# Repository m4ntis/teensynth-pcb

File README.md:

# teensynth-pcb
KiCad PCB schematics for teensynth

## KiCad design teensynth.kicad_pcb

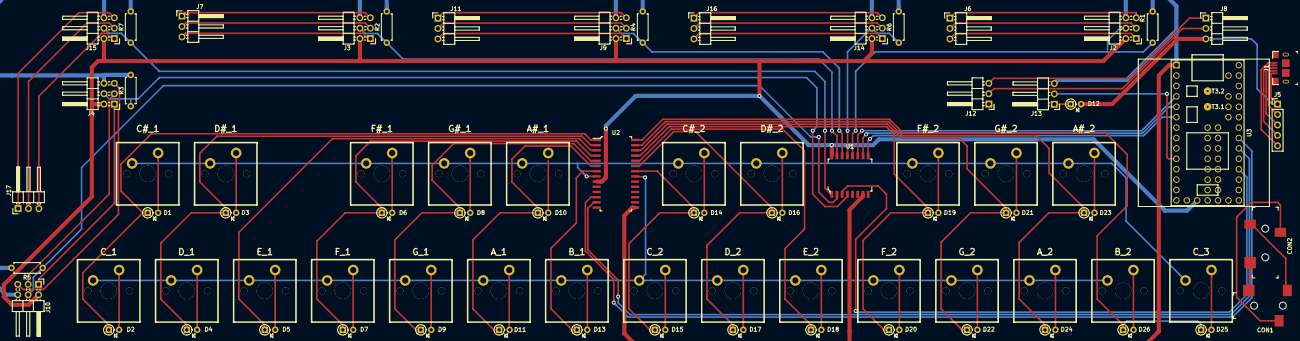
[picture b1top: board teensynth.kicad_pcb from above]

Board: 2 copper layers, 80 parts (0 on the bottom side), 86 nets.

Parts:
CON1, CON2: SJ-3523-SMT-TR; Switch_Slide_11.6x4mm_SJ-3523-SMT
D1, D2, D3, D4, D5, D6, D7, D8, D9, D10, D11, D12, D13, D14, D15, D16, D17, D18, D19, D20, D21, D22, D23, D24, D25, D26: D; D_DO-35_SOD27_P2.54mm_Vertical_AnodeUp
J1: 10118193-0001LF; USB_Micro_B_Female_10118193-0001LF
J2: Control_LED_0_O; Pin_Header_Angled_2x03_Pitch2.54mm
J3: Control_LED_3_O; Pin_Header_Angled_2x03_Pitch2.54mm
J4: Control_LED_6_I; Pin_Header_Angled_2x03_Pitch2.54mm
J5: USB; Pin_Header_Straight_1x05_Pitch2.54mm
J6: LED_1_I; Pin_Header_Angled_1x03_Pitch2.54mm
J7: LED_4_I; Pin_Header_Angled_1x03_Pitch2.54mm
J8: LED_0_I; Pin_Header_Angled_1x03_Pitch2.54mm
J9: Control_LED_2_O; Pin_Header_Angled_2x03_Pitch2.54mm
J10: Control_LED_5_O; Pin_Header_Angled_2x03_Pitch2.54mm
J11: LED_3_I; Pin_Header_Angled_1x03_Pitch2.54mm
J12: LED_X_O; Pin_Header_Angled_1x03_Pitch2.54mm
J13: LED_X_I; Pin_Header_Angled_1x03_Pitch2.54mm
J14: Control_LED_1_O; Pin_Header_Angled_2x03_Pitch2.54mm
J15: Control_LED_4_O; Pin_Header_Angled_2x03_Pitch2.54mm
J16: LED_2_I; Pin_Header_Angled_1x03_Pitch2.54mm
J17: LED_5_I; Pin_Header_Angled_1x03_Pitch2.54mm
R1, R2, R3, R4, R5, R6, R7: 10K; R_Axial_DIN0207_L6.3mm_D2.5mm_P7.62mm_Horizontal
S1: C#_1; MX1A
S2: C_1; MX1A
S3: D#_1; MX1A
S4: D_1; MX1A
S5: E_1; MX1A
S6: F#_1; MX1A
S7: F_1; MX1A
S8: G#_1; MX1A
S9: G_1; MX1A
S10: A#_1; MX1A
S11: A_1; MX1A
S12: B_1; MX1A
S13: C#_2; MX1A
S14: C_2; MX1A
S15: D#_2; MX1A
S16: D_2; MX1A
S17: E_2; MX1A
S18: F#_2; MX1A
S19: F_2; MX1A
S20: G#_2; MX1A
S21: G_2; MX1A
S22: A#_2; MX1A
S23: A_2; MX1A
S24: C_3; MX1A
S25: B_2; MX1A
U1: CD74HC4051E; SOIC-16_W7.5mm
U2: MCP23017-E_SP; SOIC-28_W7.5mm
U3: Teensy3.2; Teensy30_31_32_LC

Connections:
+3V3: J2.2, J3.2, J4.2, J9.2, J10.2, J14.2, J15.2, U1.16, U2.9, U2.18, U3.16
+5V: D12.2, J1.1, J5.1, J8.3
/A2: U1.3, U3.23
/Col0: D1.1, D2.1, U2.1
/Col1: D3.1, D4.1, U2.2
/Col2: D5.1, U2.3
/Col3: D6.1, D7.1, U2.4
/Col4: D8.1, D9.1, U2.5
/Col5: D10.1, D11.1, U2.6
/Col6: D13.1, U2.7
/Col7: D14.1, D15.1, U2.22
/Col8: D16.1, D17.1, U2.23
/Col9: D18.1, U2.24
/ColA: D19.1, D20.1, U2.25
/ColB: D21.1, D22.1, U2.26
/ColC: D23.1, D24.1, U2.27
/ColD: D25.1, D26.1, U2.28
/D2: U1.11, U3.4
/D3: U1.10, U3.5
/D4: U1.9, U3.6
/D8: J13.2, U3.10
/POT0: J2.4, R1.1, U1.12
/POT1: J14.4, R6.1, U1.13
/POT2: J9.4, R4.1, U1.14
/POT3: J3.4, R2.1, U1.15
/POT4: J15.4, R7.1, U1.1
/POT5: J10.4, R5.1, U1.2
/POT6: J4.4, R3.1, U1.4
/Row0: S1.1, S3.1, S6.1, S8.1, S10.1, S13.1, S15.1, S18.1, S20.1, S22.1, S24.1, U2.8
/Row1: S2.1, S4.1, S5.1, S7.1, S9.1, S11.1, S12.1, S14.1, S16.1, S17.1, S19.1, S21.1, S23.1, S25.1, U2.21
/SCL: U2.12, U3.26
/SDA: U2.13, U3.25
GND: J2.6, J3.6, J4.6, J9.6, J10.6, J13.3, J14.6, J15.6, R1.2, R2.2, R3.2, R4.2, R5.2, R6.2, R7.2, U1.6, U1.7, U1.8, U2.10, U2.15, U2.16, U2.17, U3.1
unnamed: CON1.1, CON2.1
unnamed: CON1.2, CON2.2
unnamed: CON1.3, CON2.3
unnamed: D1.2, S1.2
unnamed: D2.2, S2.2
unnamed: D3.2, S3.2
unnamed: D4.2, S4.2
unnamed: D5.2, S5.2
unnamed: D6.2, S6.2
unnamed: D7.2, S7.2
unnamed: D8.2, S8.2
unnamed: D9.2, S9.2
unnamed: D10.2, S10.2
unnamed: D11.2, S11.2
unnamed: D12.1, J13.1
unnamed: D13.2, S12.2
unnamed: D14.2, S13.2
unnamed: D15.2, S14.2
unnamed: D16.2, S15.2
unnamed: D17.2, S16.2
unnamed: D18.2, S17.2
unnamed: D19.2, S18.2
unnamed: D20.2, S19.2
unnamed: D21.2, S20.2
unnamed: D22.2, S21.2
unnamed: D23.2, S22.2
unnamed: D24.2, S23.2
unnamed: D25.2, S24.2
unnamed: D26.2, S25.2
unnamed: J1.2, J5.2
unnamed: J1.3, J5.3
unnamed: J1.4, J5.4
unnamed: J1.5, J5.5
unnamed: J2.1, J6.3
unnamed: J2.3, J6.2
unnamed: J2.5, J6.1
unnamed: J3.1, J7.3
unnamed: J3.3, J7.2
unnamed: J3.5, J7.1
unnamed: J4.1, J10.1
unnamed: J4.3, J10.3
unnamed: J4.5, J10.5
unnamed: J9.5, J11.1
unnamed: J9.3, J11.2
unnamed: J9.1, J11.3
unnamed: J8.2, J12.2
unnamed: J8.1, J12.3
unnamed: J14.1, J16.3
unnamed: J14.3, J16.2
unnamed: J14.5, J16.1
unnamed: J15.1, J17.3
unnamed: J15.3, J17.2
unnamed: J15.5, J17.1

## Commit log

2018-12-06 Add initial schema and project
2018-12-06 Update annotations and footprints
2018-12-06 Fix bad label
2018-12-06 Add initial pcb with key layout
2018-12-07 Change io expander and mux to smt components
2018-12-07 Throw everything in a reasonable place
2018-12-07 Update design rules
2018-12-07 Wire up the matrix to the io expander
2018-12-07 Clean up the labels on the diodes a bit
2019-01-13 Continue routing
2019-01-13 Remove unused control and switch around the analog multiplexer control connections
2019-01-13 Finish connecting all pcb components
2019-01-28 Move audio plug down to leave room for 2U keycap
2019-02-03 Change control and LED connectors and begin wiring
2019-02-03 Begin improving control and led connections
2019-02-22 Finish wiring nearly all new connectors
2019-03-30 Wire usb port and LED x
2019-03-30 Fix schematic annotations and switch second USB port for header
2019-03-30 Finish wiring up PCB
2019-03-30 Minor PCB improvements
